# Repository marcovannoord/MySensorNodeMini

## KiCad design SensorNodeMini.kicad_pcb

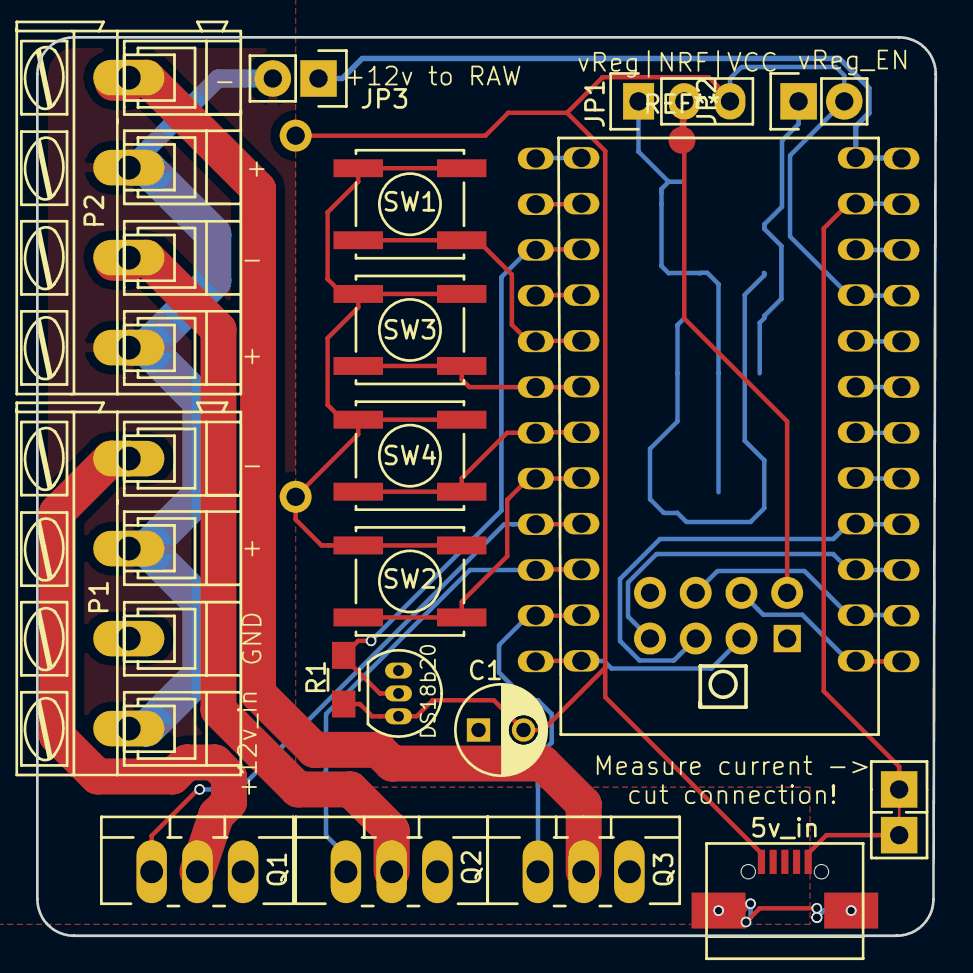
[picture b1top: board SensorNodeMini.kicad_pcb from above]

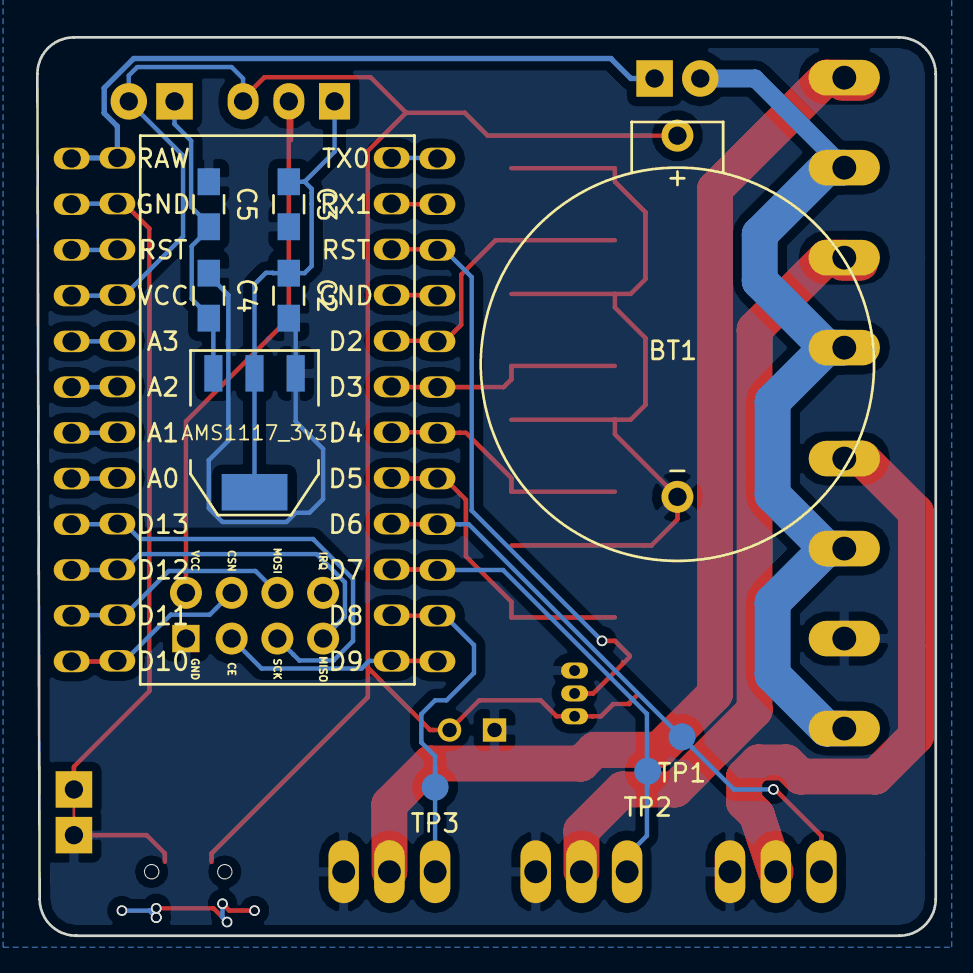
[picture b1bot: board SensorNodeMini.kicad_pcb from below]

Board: 2 copper layers, 49.9 x 49.9 mm, 28 parts (10 on the bottom side), 24 nets.

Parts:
5v_in: USB_OTG; USB_Micro-B_ebay
AMS1117_3v3: ArduinoProMini
BT1: Battery; CR3032Holder
C1: CP; C_Radial_D5_L6_P2.5
C2, C5: 10u; C_0805_HandSoldering
C3, C4: 0.1u; C_0805_HandSoldering
DS18b20: DS18B20; TO-92_Inline_Narrow_Oval
IC1: AMS1117; SOT-223
JP1: NRF_3v3_SEL; Pin_Header_Straight_1x03
JP2: vReg_EN; Pin_Header_Straight_1x02
JP3: Feed_with_raw; Pin_Header_Straight_1x02
JP4: Meas_cur; Pin_Header_Straight_1x02_cuttable
P1, P2: CONN_01X04; AK300-4
Q1, Q2, Q3: Q_NMOS_GDS; TO-220_Neutral123_Vertical_LargePads
R1: R; R_0805_HandSoldering
SW1, SW2, SW3, SW4: SW_PUSH; SW_SPST_EVPBF
TP1, TP2, TP3: Measurement_Point_Round-SMD-Pad_Small
U2: NRF24L01+

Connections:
+12V: JP3.2, P1.1, P1.3, P2.1, P2.3
CE: AMS1117_3v3.12, U2.2
CSN: AMS1117_3v3.13, U2.7
D3: AMS1117_3v3.3, DS18b20.2, R1.1
D6: AMS1117_3v3.9, Q1.1, TP1.1
D7: AMS1117_3v3.10, Q2.1, TP2.1
D8: AMS1117_3v3.11, Q3.1, TP3.1
GND: 5v_in.5, BT1.2, C1.1, C2.2, C3.2, C4.1, C5.1, DS18b20.1, IC1.1, JP4.2, P1.2, Q1.3, Q2.3, Q3.3, SW1.1, SW2.1, SW3.1, SW4.1, U2.1
MISO: AMS1117_3v3.15, U2.4
MOSI: AMS1117_3v3.14, U2.6
unnamed: C4.2, C5.2, IC1.3, JP2.1
unnamed: AMS1117_3v3.23, JP4.1
unnamed: P1.4, Q1.2
unnamed: P2.2, Q2.2
unnamed: P2.4, Q3.2
unnamed: AMS1117_3v3.5, SW1.2
unnamed: AMS1117_3v3.8, SW2.2
unnamed: AMS1117_3v3.6, SW3.2
unnamed: AMS1117_3v3.7, SW4.2
RAW: AMS1117_3v3.24, JP3.1
SCK: AMS1117_3v3.16, U2.3
VCC: 5v_in.1, AMS1117_3v3.21, BT1.1, C1.2, DS18b20.3, JP1.3, JP2.2, R1.2
VCC_NRF: JP1.2, U2.8
Vout: C2.1, C3.1, IC1.2, JP1.1

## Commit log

2016-07-23 First commit: imported library, added pro mini footprints, and first layout of PCB
2016-07-25 added 3 mosfets, battery and connectors.
2016-07-25 routed everything, made gerbers.
2016-10-20 v0.1, added microusb, removed some bugs, cleaned up the board
2016-10-20 nicely rounded edges:)
